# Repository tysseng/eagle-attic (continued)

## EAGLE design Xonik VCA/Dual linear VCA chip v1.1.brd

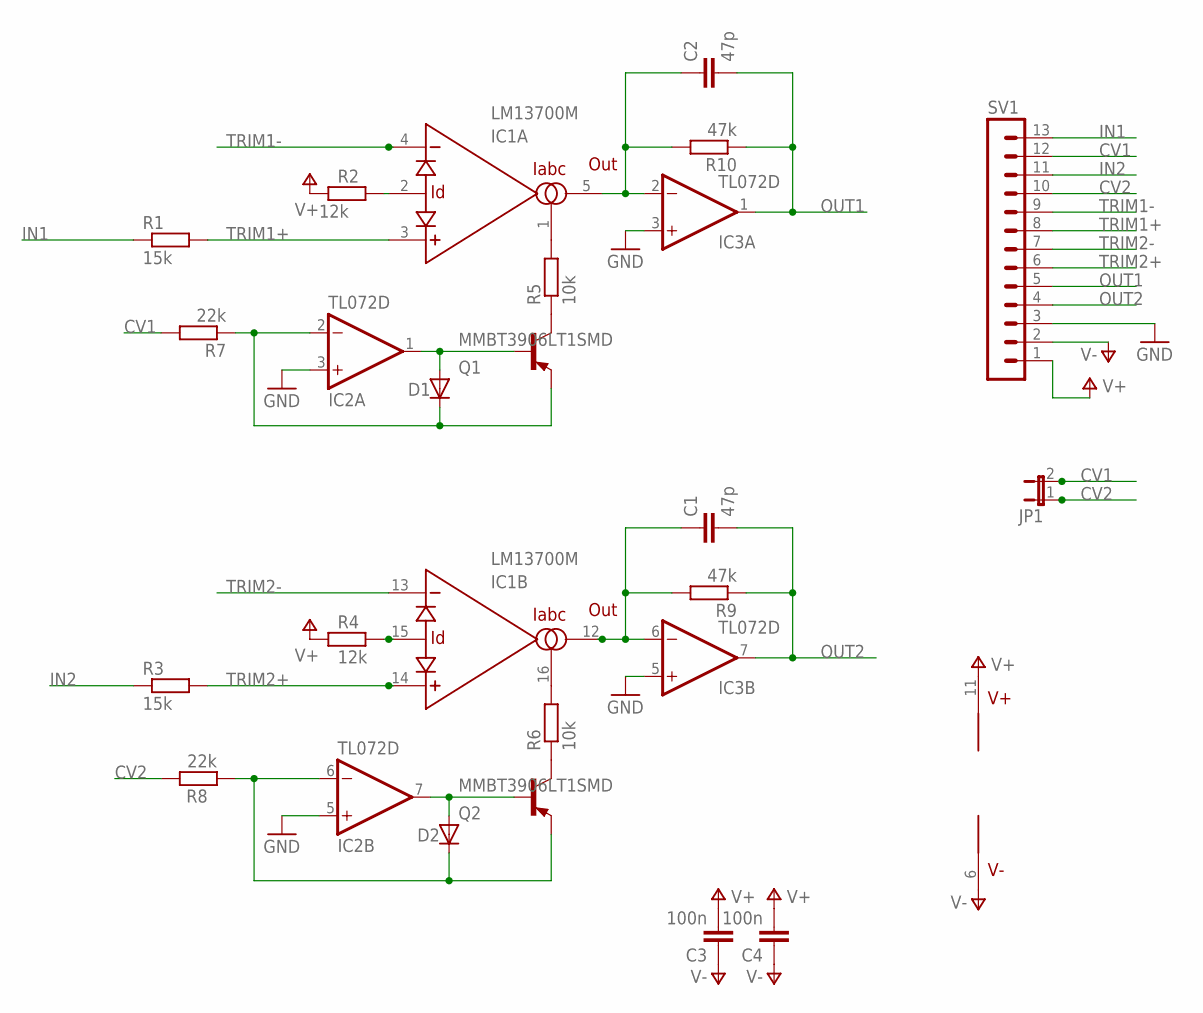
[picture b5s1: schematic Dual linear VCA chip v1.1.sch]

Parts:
C1, C2: 47p; C0805
C3, C4: 100n; C0805
D1, D2: DIODE-SOD80C; SOD80C
IC1: LM13700M; SO16
IC2, IC3: TL072D; SO08
JP1: JP1E; JP1
Q1, Q2: MMBT3906LT1SMD; SOT23-BEC
R1, R3: 15k; R0805
R2, R4: 12k; R0805
R5, R6: 10k; R0805
R7, R8: 22k; R0805
R9, R10: 47k; R0805
SV1: MA13-1

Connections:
CV1: JP1.2, R7.2, SV1.12
CV2: JP1.1, R8.2, SV1.10
GND: IC2.3 (+IN), IC2.5 (+IN), IC3.3 (+IN), IC3.5 (+IN), SV1.3
IN1: R1.1, SV1.13
IN2: R3.1, SV1.11
unnamed: Q1.C, R5.1
unnamed: Q2.C, R6.1
unnamed: D1.C, IC2.2 (-IN), Q1.E, R7.1
unnamed: IC1.1 (IABC), R5.2
unnamed: IC1.2 (ID), R2.2
unnamed: D2.A, IC2.7 (OUT), Q2.B
unnamed: C2.1, IC1.5 (OUT), IC3.2 (-IN), R10.2
unnamed: D1.A, IC2.1 (OUT), Q1.B
unnamed: D2.C, IC2.6 (-IN), Q2.E, R8.1
unnamed: IC1.16 (IABC), R6.2
unnamed: IC1.15 (ID), R4.2
unnamed: C1.1, IC1.12 (OUT), IC3.6 (-IN), R9.2
OUT1: C2.2, IC3.1 (OUT), R10.1, SV1.5
OUT2: C1.2, IC3.7 (OUT), R9.1, SV1.4
TRIM1+: IC1.3 (+IN), R1.2, SV1.8
TRIM1-: IC1.4 (-IN), SV1.9
TRIM2+: IC1.14 (+IN), R3.2, SV1.6
TRIM2-: IC1.13 (-IN), SV1.7
V+: C3.2, C4.2, IC1.11 (V+), IC2.8 (V+), IC3.8 (V+), R2.1, R4.1, SV1.1
V-: C3.1, C4.1, IC1.6 (V-), IC2.4 (V-), IC3.4 (V-), SV1.2

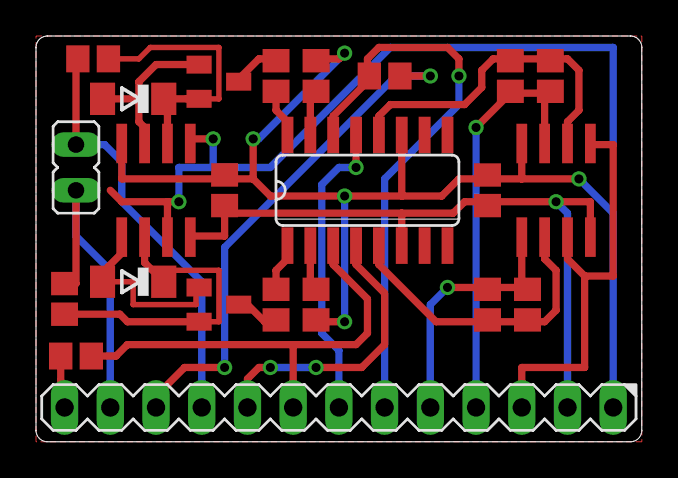
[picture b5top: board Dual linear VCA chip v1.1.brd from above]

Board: 2 copper layers, 33.7 x 22.5 mm, 23 parts (0 on the bottom side), 25 nets.

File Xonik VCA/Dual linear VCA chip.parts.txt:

Partlist

Exported from Dual linear VCA chip.sch at 25.02.2014 19:18:17

EAGLE Version 6.4.0 Copyright (c) 1988-2013 CadSoft

Assembly variant: 

Part     Value          Device         Package   Library        Sheet

C1       47p            C-EUC0805      C0805     resistor       1
C2       47p            C-EUC0805      C0805     resistor       1
C3       100n           C-EUC0805      C0805     resistor       1
C4       100n           C-EUC0805      C0805     resistor       1
D1                      DIODE-SOD80C   SOD80C    diode          1
D2                      DIODE-SOD80C   SOD80C    diode          1
IC1      LM13700M       LM13700M       SO16      synthdiy       1
IC2      TL072D         TL072D         SO08      linear         1
IC3      TL072D         TL072D         SO08      linear         1
JP1                     JP1E           JP1       jumper         1
Q1       MMBT3906LT1SMD MMBT3906LT1SMD SOT23-BEC transistor-pnp 1
Q2       MMBT3906LT1SMD MMBT3906LT1SMD SOT23-BEC transistor-pnp 1
R1       15k            R-EU_R0805     R0805     resistor       1
R2       12k            R-EU_R0805     R0805     resistor       1
R3       15k            R-EU_R0805     R0805     resistor       1
R4       12k            R-EU_R0805     R0805     resistor       1
R5       10k            R-EU_R0805     R0805     resistor       1
R6       10k            R-EU_R0805     R0805     resistor       1
R7       22k            R-EU_R0805     R0805     resistor       1
R8       22k            R-EU_R0805     R0805     resistor       1
R9       47k            R-EU_R0805     R0805     resistor       1
R10      47k            R-EU_R0805     R0805     resistor       1
SV1                     MA13-1         MA13-1    con-lstb       1
